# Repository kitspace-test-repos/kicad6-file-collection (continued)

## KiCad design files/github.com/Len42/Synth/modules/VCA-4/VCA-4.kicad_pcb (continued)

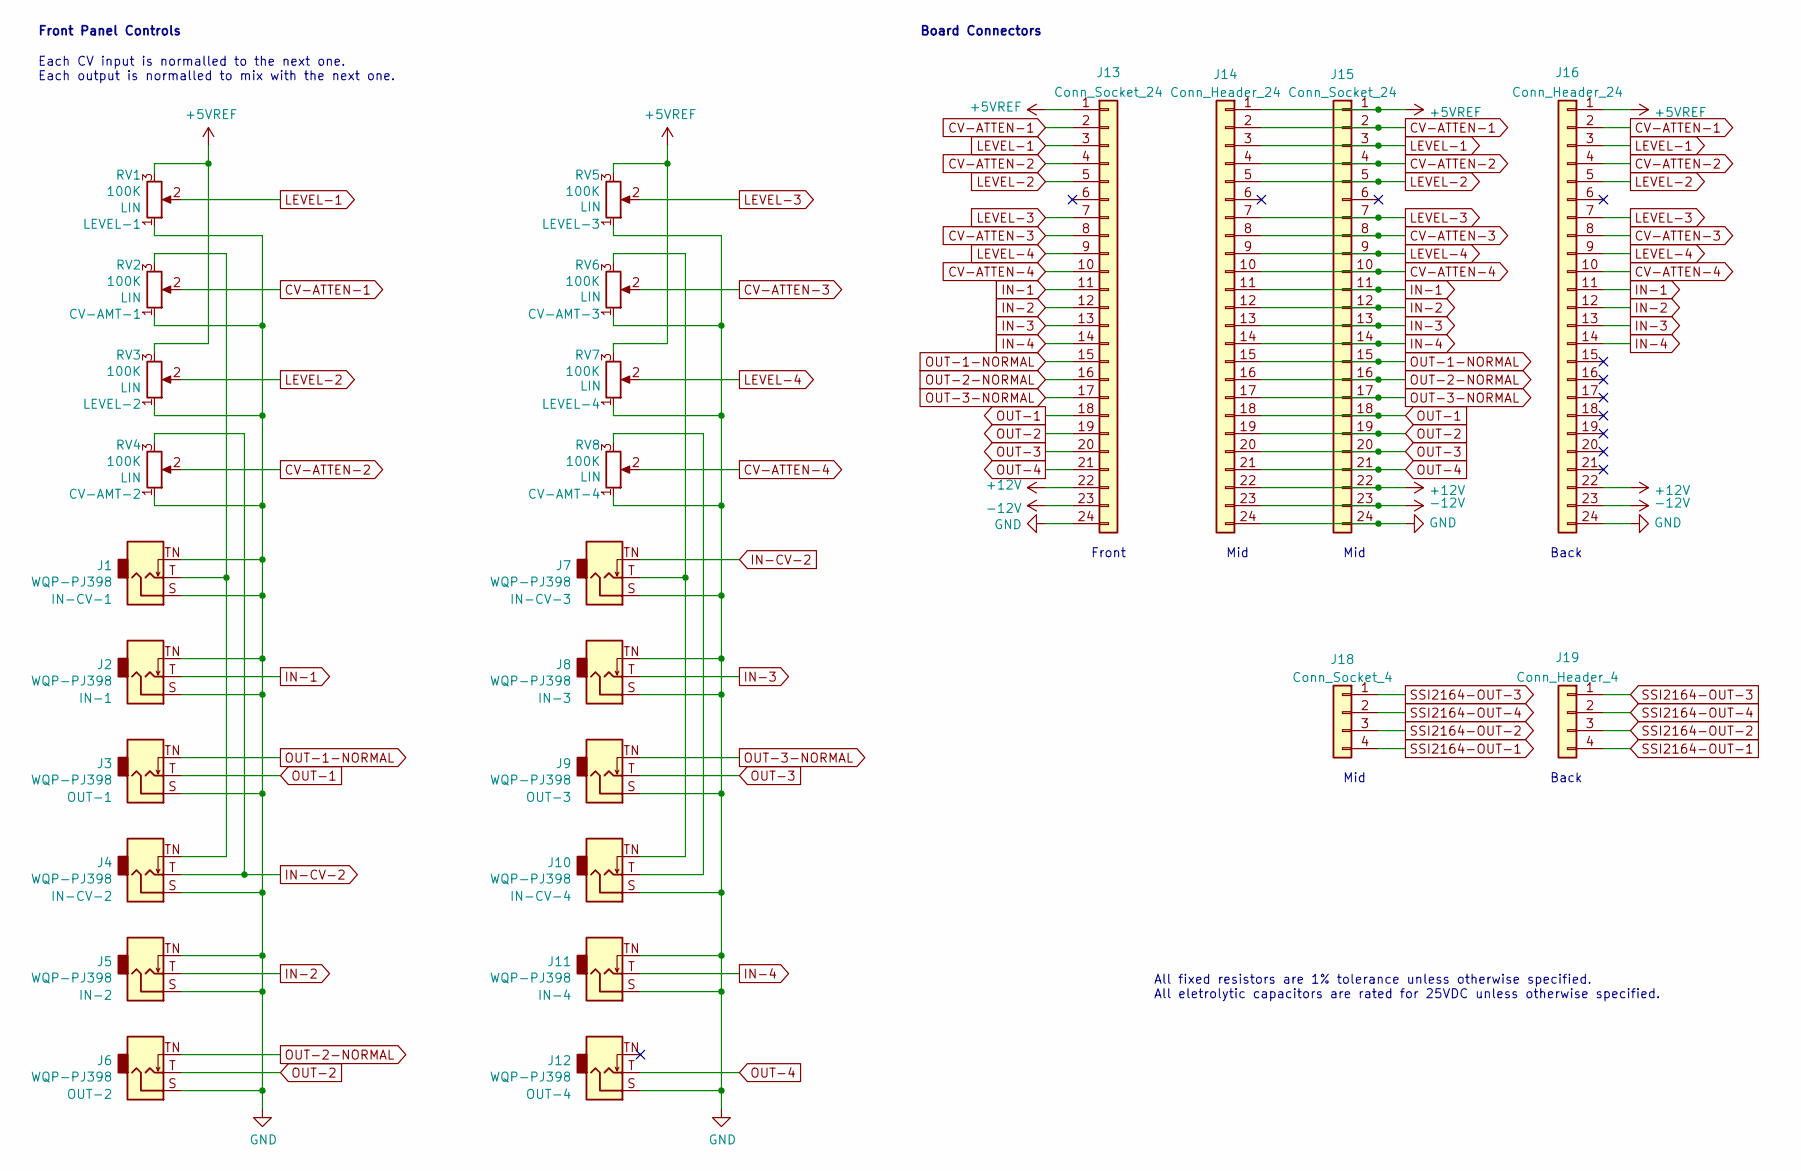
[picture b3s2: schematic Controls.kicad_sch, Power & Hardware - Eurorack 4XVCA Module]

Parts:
J1, J2, J3, J4, J5, J6, J7, J8, J9, J10, J11, J12: WQP-PJ398; Jack_3.5mm_QingPu_WQP-PJ398SM_Vertical; ManufacturerPartNum PJ398SM / WQP518MA
J13, J15: Conn_Socket_24; PinSocket_1x24_P2.54mm_Vertical
J14, J16: Conn_Header_24; PinHeader_1x24_P2.54mm_Vertical
J18: Conn_Socket_4; PinSocket_1x04_P2.54mm_Vertical
J19: Conn_Header_4; PinHeader_1x04_P2.54mm_Vertical
RV1, RV3, RV5, RV7: 100K; Potentiometer_Alpha_RD901F-40-00D_Single_Vertical; ManufacturerPartNum RD901F-40-15R1-B100K-00DL1
RV2, RV4, RV6, RV8: 100K; Potentiometer_SongHuei_Single_Vertical; ManufacturerPartNum R0904N*

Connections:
+5VREF: J13.1, J14.1, J15.1, J16.1, RV1.3, RV3.3, RV5.3, RV7.3; also elsewhere on the board
+12V: J13.22, J14.22, J15.22, J16.22; also elsewhere on the board
-12V: J13.23, J14.23, J15.23, J16.23; also elsewhere on the board
CV-ATTEN-1: J13.2, J14.2, J15.2, J16.2, RV2.2; also elsewhere on the board
CV-ATTEN-2: J13.4, J14.4, J15.4, J16.4, RV4.2; also elsewhere on the board
CV-ATTEN-3: J13.8, J14.8, J15.8, J16.8, RV6.2; also elsewhere on the board
CV-ATTEN-4: J13.10, J14.10, J15.10, J16.10, RV8.2; also elsewhere on the board
GND: J1.S, J1.TN, J2.S, J2.TN, J3.S, J4.S, J5.S, J5.TN, J6.S, J7.S, J8.S, J8.TN, J9.S, J10.S, J11.S, J11.TN, J12.S, J13.24, J14.24, J15.24, J16.24, RV1.1, RV2.1, RV3.1, RV4.1, RV5.1, RV6.1, RV7.1, RV8.1; also elsewhere on the board
IN-1: J2.T, J13.11, J14.11, J15.11, J16.11; also elsewhere on the board
IN-2: J5.T, J13.12, J14.12, J15.12, J16.12; also elsewhere on the board
IN-3: J8.T, J13.13, J14.13, J15.13, J16.13; also elsewhere on the board
IN-4: J11.T, J13.14, J14.14, J15.14, J16.14; also elsewhere on the board
IN-CV-2: J4.T, J7.TN, RV4.3
LEVEL-1: J13.3, J14.3, J15.3, J16.3, RV1.2; also elsewhere on the board
LEVEL-2: J13.5, J14.5, J15.5, J16.5, RV3.2; also elsewhere on the board
LEVEL-3: J13.7, J14.7, J15.7, J16.7, RV5.2; also elsewhere on the board
LEVEL-4: J13.9, J14.9, J15.9, J16.9, RV7.2; also elsewhere on the board
unnamed: J1.T, J4.TN, RV2.3
unnamed: J10.T, RV8.3
unnamed: J7.T, J10.TN, RV6.3
OUT-1: J3.T, J13.18, J14.18, J15.18; also elsewhere on the board
OUT-1-NORMAL: J3.TN, J13.15, J14.15, J15.15; also elsewhere on the board
OUT-2: J6.T, J13.19, J14.19, J15.19; also elsewhere on the board
OUT-2-NORMAL: J6.TN, J13.16, J14.16, J15.16; also elsewhere on the board
OUT-3: J9.T, J13.20, J14.20, J15.20; also elsewhere on the board
OUT-3-NORMAL: J9.TN, J13.17, J14.17, J15.17; also elsewhere on the board
OUT-4: J12.T, J13.21, J14.21, J15.21; also elsewhere on the board
SSI2164-OUT-1: J18.4, J19.4; also elsewhere on the board
SSI2164-OUT-2: J18.3, J19.3; also elsewhere on the board
SSI2164-OUT-3: J18.1, J19.1; also elsewhere on the board
SSI2164-OUT-4: J18.2, J19.2; also elsewhere on the board

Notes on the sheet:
All fixed resistors are 1% tolerance unless otherwise specified. All eletrolytic capacitors are rated for 25VDC unless otherwise specified.
Back
Mid
Board Connectors
Each CV input is normalled to the next one. Each output is normalled to mix with the next one.
Front
Front Panel Controls

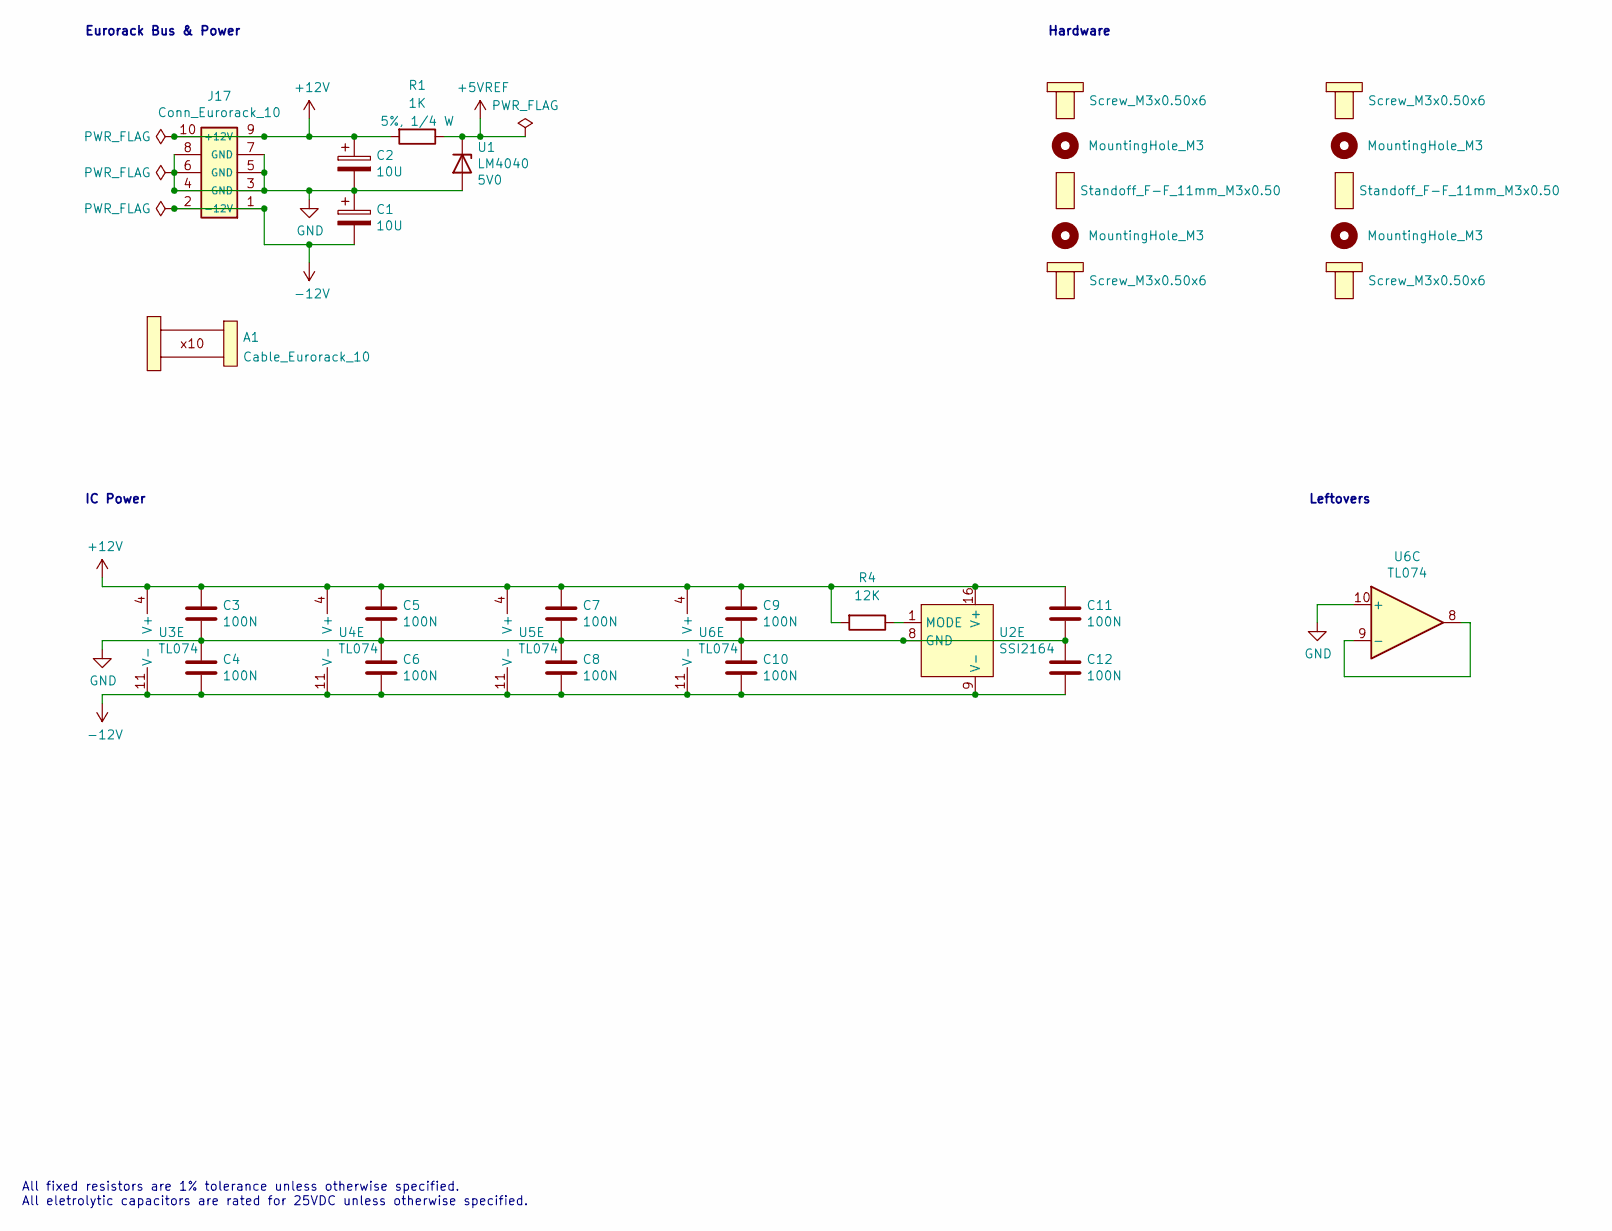
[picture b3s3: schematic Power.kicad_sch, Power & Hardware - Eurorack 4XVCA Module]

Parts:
A1: Cable_Eurorack_10; NoFootprint
C1, C2: 10U; CP_Radial_D4.0mm_P1.50mm; ManufacturerPartNum EEA-FC1E100
C3, C4, C5, C6, C7, C8, C9, C10, C11, C12: 100N; C_Disc_D5.0mm_W2.5mm_P2.50mm; ManufacturerPartNum FG18X7R1H104KNT06
H1, H5, H6, H10: Screw_M3x0.50x6
H2, H4, H7, H9: MountingHole_M3; MountingHole_PCB_3.2mm_M3
H3, H8: Standoff_F-F_11mm_M3x0.50; ManufacturerPartNum 05.03.111
J17: Conn_Eurorack_10; IDC-Header-Eurorack-10-TH; ManufacturerPartNum 61201021621
R1: 1K; R_Axial_DIN0207_L6.3mm_D2.5mm_P10.16mm_Horizontal; ManufacturerPartNum CCF071K00JKE36
R4: 12K; R_Axial_DIN0207_L6.3mm_D2.5mm_P7.62mm_Horizontal; ManufacturerPartNum MFR-12FTF52-12K
U1: LM4040; TO-92-2_Wide; ManufacturerPartNum LM4040BIZ-5.0/NOPB
U2: SSI2164; Breakout_DIP-SOIC-16_W15.24mm; ManufacturerPartNum SSI2164
U3, U4, U5, U6: TL074; DIP-14_W7.62mm; ManufacturerPartNum TL074BCN

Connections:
+5VREF: R1.1, U1.1 (K); also elsewhere on the board
+12V: C2.1, C3.1, C5.1, C7.1, C9.1, C11.1, J17.9 (+12V), J17.10, R1.2, R4.2, U2.16 (V+), U3.4 (V+), U4.4 (V+), U5.4 (V+), U6.4 (V+); also elsewhere on the board
-12V: C1.2, C4.2, C6.2, C8.2, C10.2, C12.2, J17.1 (-12V), J17.2, U2.9 (V-), U3.11 (V-), U4.11 (V-), U5.11 (V-), U6.11 (V-); also elsewhere on the board
GND: C1.1, C2.2, C3.2, C4.1, C5.2, C6.1, C7.2, C8.1, C9.2, C10.1, C11.2, C12.1, J17.3 (GND), J17.4, J17.5 (GND), J17.6, J17.7 (GND), J17.8, U1.2 (A), U2.8 (GND), U6.10 (+); also elsewhere on the board
unnamed: R4.1, U2.1 (MODE)
unnamed: U6.8, U6.9 (-)

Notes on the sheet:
IC Power
Leftovers
Eurorack Bus & Power
All fixed resistors are 1% tolerance unless otherwise specified. All eletrolytic capacitors are rated for 25VDC unless otherwise specified.
Hardware

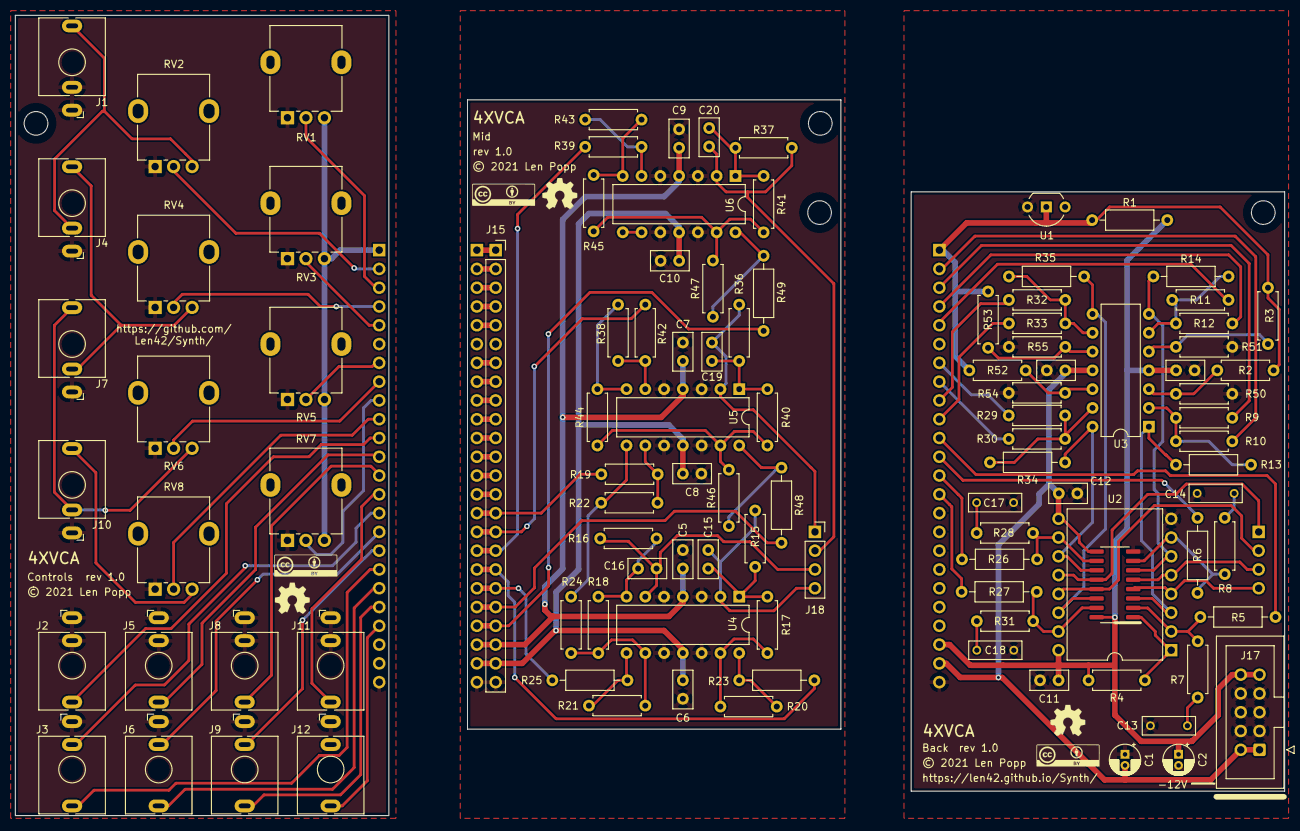
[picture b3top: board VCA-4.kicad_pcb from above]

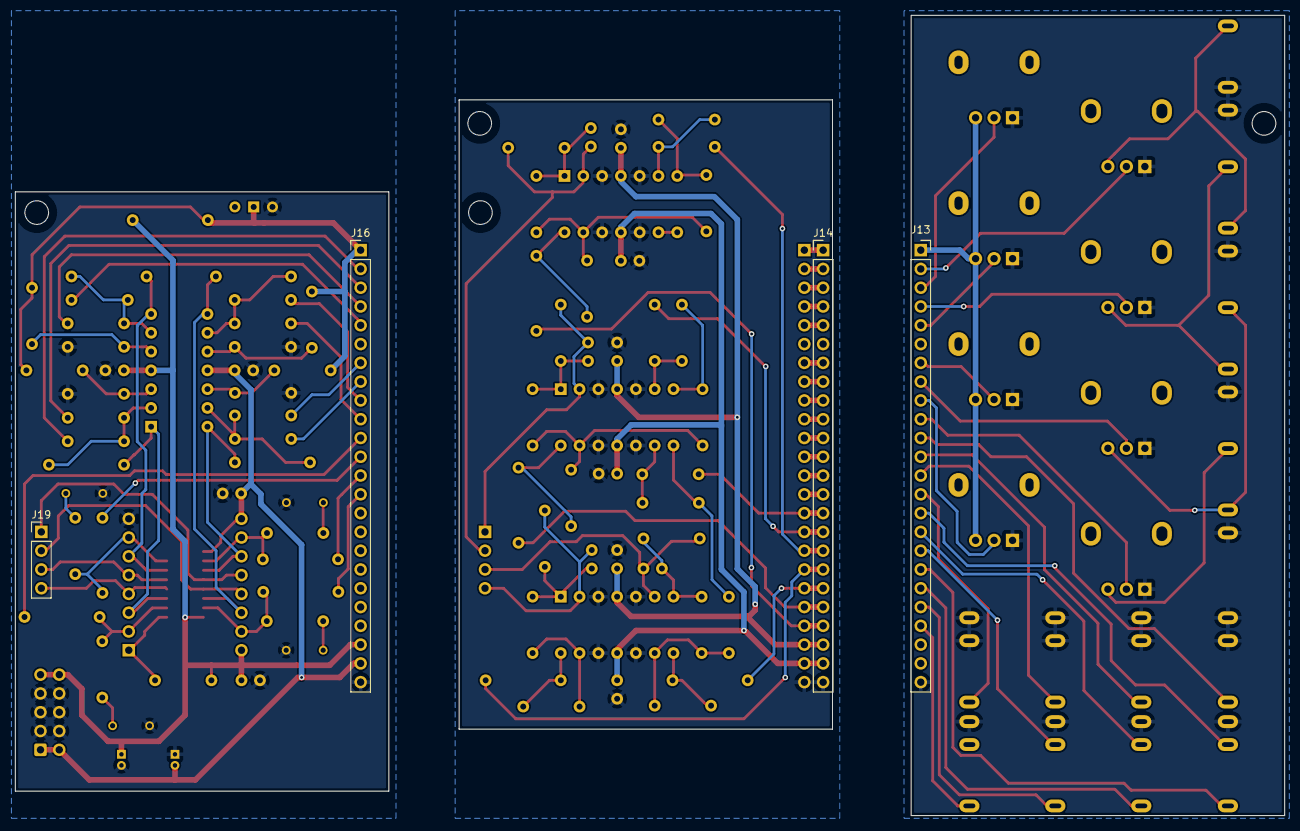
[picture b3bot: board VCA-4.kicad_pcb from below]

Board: 2 copper layers, 171.6 x 108.2 mm, 118 parts (4 on the bottom side), 71 nets.

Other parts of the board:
G2, G2#2, G2#3: Logo_CC_BY
G4, G4#2, G4#3: Logo_OSHW

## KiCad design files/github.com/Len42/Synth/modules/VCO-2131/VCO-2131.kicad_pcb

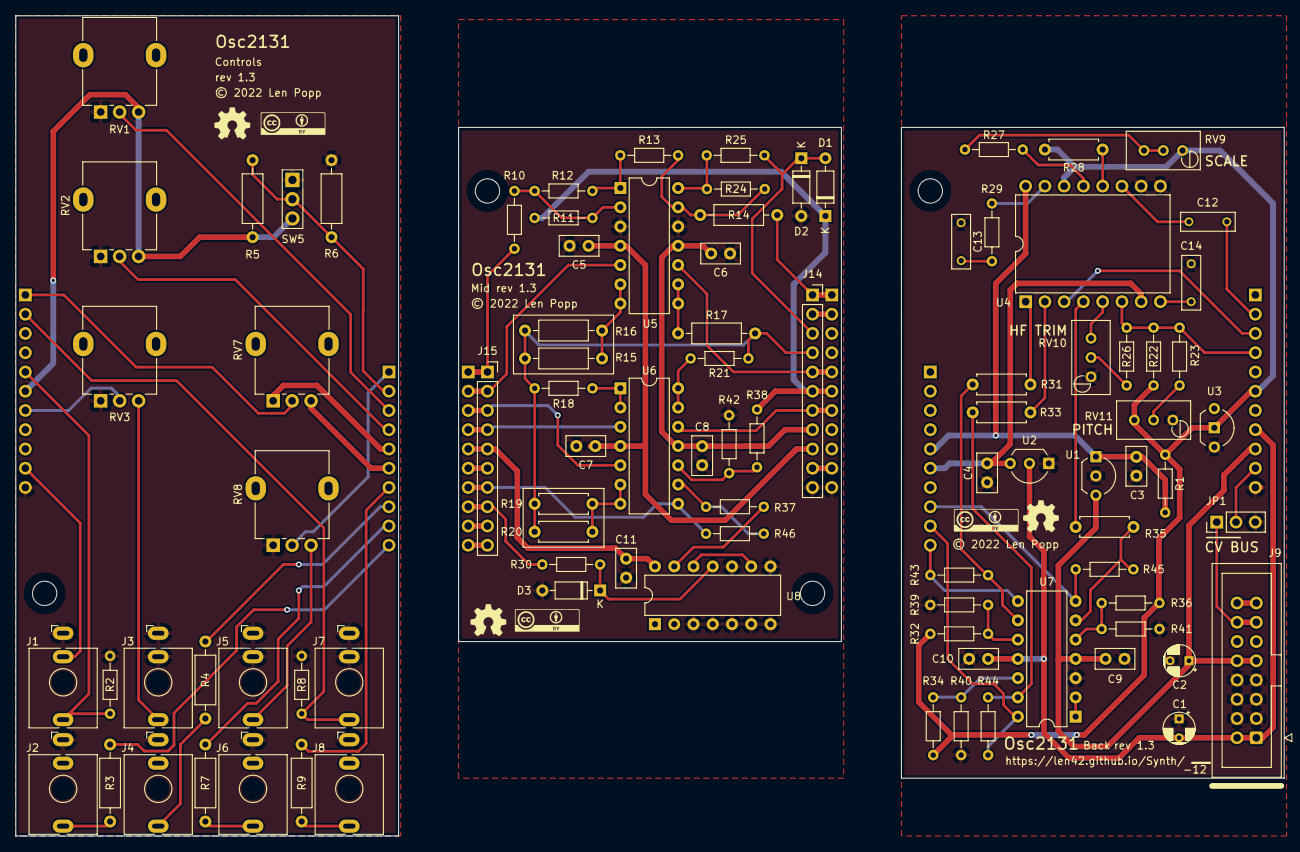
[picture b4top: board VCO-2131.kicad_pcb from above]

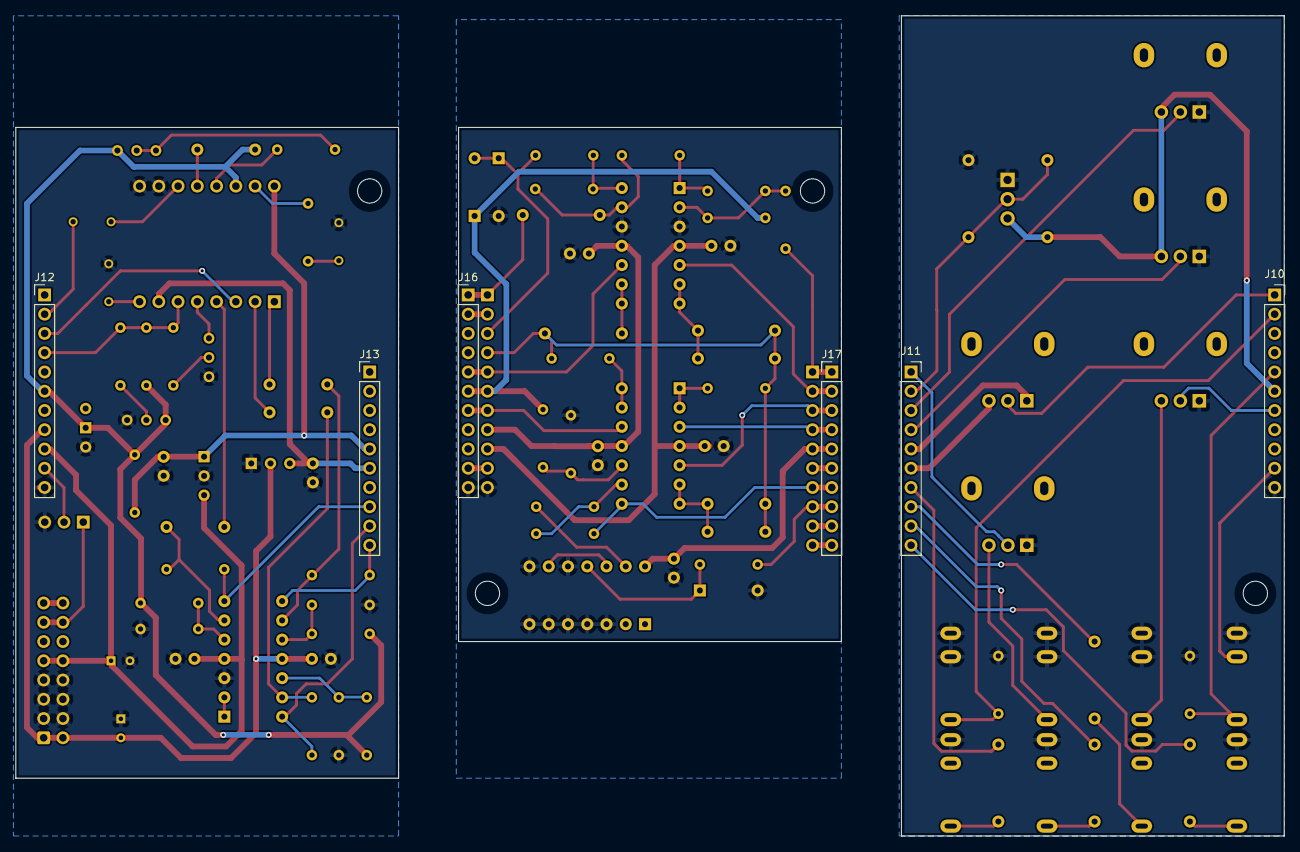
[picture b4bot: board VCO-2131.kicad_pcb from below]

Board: 2 copper layers, 167.3 x 108.2 mm, 104 parts (6 on the bottom side), 63 nets.

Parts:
C1, C2: 10U; CP_Radial_D4.0mm_P2.50mm
C3, C4, C5, C6, C7, C8, C9, C10, C11: 100N; C_Disc_D5.0mm_W2.5mm_P2.50mm
C12, C13: 10N; C_Rect_Kemet_L7.2mm_W2.5mm_P5mm
C14: 3N9; C_Rect_Kemet_L7.2mm_W2.5mm_P5mm
D1, D2, D3: 1N5711; D_DO-35_SOD27_P7.62mm_Horizontal
G1, G6: Logo_CC_BY
G2, G3, G4: Logo_OSHW
G5: Logo_CC_BY_SA; Logo_CC_BY
J1, J2, J3, J4, J5, J6, J7, J8: WQP-PJ398; Jack_3.5mm_QingPu_WQP-PJ398SM_Vertical
J9: Conn_Eurorack_16; IDC-Header-Eurorack-16-TH
J10: Conn_Front_Left; PinSocket_1x11_P2.54mm_Vertical
J11: Conn_Front_Right; PinSocket_1x10_P2.54mm_Vertical
J12: Conn_Back_Right; PinHeader_1x11_P2.54mm_Vertical
J13: Conn_Back_Left; PinHeader_1x10_P2.54mm_Vertical
J14: Conn_Passthru_Right; PinSocket_1x11_P2.54mm_Vertical
J15: Conn_Passthru_Left; PinSocket_1x10_P2.54mm_Vertical
J16: Conn_Mid_Right; PinHeader_1x11_P2.54mm_Vertical
J17: Conn_Mid_Left; PinHeader_1x10_P2.54mm_Vertical
JP1: CV-BUS; PinHeader_1x03_P2.54mm_Vertical
R1: 470R; R_Axial_DIN0204_L3.6mm_D1.6mm_P7.62mm_Horizontal
R2: 4M7; R_Axial_DIN0204_L3.6mm_D1.6mm_P7.62mm_Horizontal
R3, R4, R7, R9: 1K; R_Axial_DIN0207_L6.3mm_D2.5mm_P10.16mm_Horizontal
R5, R6, R17: 100K; R_Axial_DIN0207_L6.3mm_D2.5mm_P10.16mm_Horizontal
R8, R21, R22, R23, R25: 100K; R_Axial_DIN0204_L3.6mm_D1.6mm_P7.62mm_Horizontal
R10, R13: 150K; R_Axial_DIN0204_L3.6mm_D1.6mm_P7.62mm_Horizontal
R11, R12, R24: 75K; R_Axial_DIN0204_L3.6mm_D1.6mm_P7.62mm_Horizontal
R14: 300K; R_Axial_DIN0207_L6.3mm_D2.5mm_P10.16mm_Horizontal
R15, R16: 125K; R_Axial_DIN0207_L6.3mm_D2.5mm_P10.16mm_Horizontal
R18: 62K; R_Axial_DIN0204_L3.6mm_D1.6mm_P7.62mm_Horizontal
R19, R20: 1M5; R_Axial_DIN0207_L6.3mm_D2.5mm_P7.62mm_Horizontal
R26: 270K; R_Axial_DIN0204_L3.6mm_D1.6mm_P7.62mm_Horizontal
R27: 47K; R_Axial_DIN0204_L3.6mm_D1.6mm_P7.62mm_Horizontal
R28: 499K; R_Axial_DIN0207_L6.3mm_D2.5mm_P7.62mm_Horizontal
R29: 270R; R_Axial_DIN0204_L3.6mm_D1.6mm_P7.62mm_Horizontal
R30: 10K; R_Axial_DIN0204_L3.6mm_D1.6mm_P7.62mm_Horizontal
R31, R33, R35: 9K; R_Axial_DIN0207_L6.3mm_D2.5mm_P7.62mm_Horizontal
R32, R34, R36, R42, R43, R44, R45, R46: 36K; R_Axial_DIN0204_L3.6mm_D1.6mm_P7.62mm_Horizontal
R37, R38: 18K; R_Axial_DIN0204_L3.6mm_D1.6mm_P7.62mm_Horizontal
R39, R40, R41: 24K; R_Axial_DIN0204_L3.6mm_D1.6mm_P7.62mm_Horizontal
RV1, RV2, RV3, RV7, RV8: 100K; Potentiometer_Alpha_RD901F-40-00D_Single_Vertical
RV9, RV10, RV11: 5K; Potentiometer_Bourns_3296W_Vertical
SW5: ON_OFF_ON; SW_SPDT_THT_2.54
U1: L78L05; TO-92_Inline_Wide
U2: L79L05; TO-92_Inline_Wide
U3: LM4040; TO-92-2_Wide
U4: SSI2131; Breakout_DIP-16_W15.24mm
U5, U6, U7: TL074; DIP-14_W7.62mm
U8: CD4013; DIP-14_W7.62mm

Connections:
+5V: C3.1, C11.1, J11.5, J13.5, J15.5, J17.5, R1.2, RV7.1, U1.1 (VO), U4.16 (V+), U8.14 (VDD)
+12V: C2.1, C5.1, C7.1, C9.1, J9.9 (+12V), J9.10, J12.9, J14.9, U1.3 (VI), U5.4 (V+), U6.4 (V+), U7.4 (V+)
-5V: C4.2, J11.6, J13.6, J15.6, J17.6, RV7.3, U2.3 (VO), U4.7 (V-)
-12V: C1.2, C6.2, C8.2, C10.2, J9.1 (-12V), J9.2, J12.8, J14.8, U2.2 (VI), U5.11 (V-), U6.11 (V-), U7.11 (V-)
CV-FREQ-1VOCT: J1.T, J10.5, J14.5, J16.5, R2.1, U5.10 (+)
CV-FREQ-BUS: J1.TN, J10.10, J12.10, J14.10, J16.10, JP1.2 (C)
CV-FREQ-COARSE: J11.4, J15.4, J17.4, RV2.2, U6.3 (+)
CV-FREQ-FINE: J11.3, J15.3, J17.3, RV1.2, U6.5 (+)
CV-FREQ-MOD: J10.7, J14.7, J16.7, RV3.2, U6.12 (+)
CV-FREQ-MOD-IN: J3.T, RV3.3
CV-FREQ-OCTAVE: J11.2, J15.2, J17.2, R5.2, R6.2, SW5.2, U5.5 (+)
CV-PW-MOD: J11.1, J15.1, J17.1, R10.2, RV8.2
CV-PW-MOD-IN: J5.T, RV8.3
CV-PW-POT: J10.1, J14.1, J16.1, R14.2, RV7.2
EXPO-FREQ-2131: J12.4, J14.4, R15.1, R16.1, R17.1, R18.1, R19.1, R20.1, R21.1, R22.1, R23.1, R26.2, U4.6 (EXPO-FREQ)
GND: C1.1, C2.2, C3.2, C4.1, C5.2, C6.1, C7.2, C8.1, C9.2, C10.1, C11.2, C13.1, C14.2, D2.2 (A), D3.2 (A), J1.S, J2.S, J3.S, J3.TN, J4.S, J5.S, J5.TN, J6.S, J7.S, J7.TN, J8.S, J9.3 (GND), J9.4, J9.5 (GND), J9.6, J9.7 (GND), J9.8, J10.11, J12.11, J14.11, J16.11, JP1.3 (B), R2.2, R6.1, R8.2, R39.2, R40.2, R41.2, R42.2, RV1.1, RV2.1, RV3.1, RV8.1, RV10.1, RV11.1, SW5.1, U1.2 (GND), U2.1 (GND), U3.2 (A), U4.9 (GND), U4.10 (SYNC-H), U5.3 (+), U5.12 (+), U7.3 (+), U8.3 (C), U8.4 (R), U8.5 (D), U8.6 (S), U8.7 (VSS), U8.8 (S), U8.10 (R)
IN-SYNC: C12.1, J7.T, J10.2, J12.2, J14.2, J16.2, R8.1
unnamed: C12.2, U4.11 (SYNC-S)
unnamed: C13.2, R29.2
unnamed: C14.1, U4.8 (TCAP)
unnamed: D3.1 (K), R30.1, U8.11 (C)
unnamed: J2.T, R3.2
unnamed: J4.T, R4.2
unnamed: J6.T, R7.2
unnamed: J8.T, R9.2
unnamed: J9.13 (CV), J9.14, JP1.1 (A)
unnamed: J9.15 (GATE), J9.16
unnamed: R10.1, R11.1, R12.2, U5.2 (-)
unnamed: R12.1, R13.2, U5.1
unnamed: R13.1, R14.1, R24.2, U5.13 (-)
unnamed: R15.2, R16.2, U5.6 (-), U5.7
unnamed: R17.2, U5.8, U5.9 (-)
unnamed: R18.2, U6.1, U6.2 (-)
unnamed: R19.2, R20.2, U6.6 (-), U6.7
unnamed: R21.2, U6.13 (-), U6.14
unnamed: R23.2, RV11.2
unnamed: R24.1, R25.2, U5.14
unnamed: R26.1, RV10.2
unnamed: R27.1, RV9.2, RV9.3
unnamed: R27.2, U4.13 (EXPO-SCALE)
unnamed: R28.1, U4.12 (LIN-FREQ)
unnamed: R29.1, U4.15 (BW-COMP)
unnamed: R31.1, R43.2, U7.9 (-)
unnamed: R31.2, U4.1 (SAW)
unnamed: R32.1, R39.1, U7.10 (+)
unnamed: R33.1, R44.2, U7.13 (-)
unnamed: R33.2, U4.2 (PULSE)
unnamed: R34.1, R40.1, U7.12 (+)
unnamed: R35.1, R45.2, U7.6 (-)
unnamed: R35.2, U4.4 (TRI)
unnamed: R36.1, R41.1, U7.5 (+)
unnamed: R37.1, R46.2, U6.9 (-)
unnamed: R37.2, U8.13 (Q)
unnamed: R38.1, R42.1, U6.10 (+)
unnamed: RV10.3, U4.5 (HF-TRACK)
unnamed: U7.1, U7.2 (-)
unnamed: U8.9 (D), U8.12 (~Q)
OUT-PULSE: J11.9, J13.9, J15.9, J17.9, R7.1, R44.1, U7.14
OUT-SAW: J11.10, J13.10, J15.10, J17.10, R3.1, R43.1, U7.8
OUT-SUB: J11.7, J15.7, J17.7, R9.1, R46.1, U6.8
OUT-TRI: J11.8, J13.8, J15.8, J17.8, R4.1, R30.2, R45.1, U7.7
PWM-2131: D1.2 (A), D2.1 (K), J12.3, J14.3, R25.1, U4.3 (PWM)
VREF+: D1.1 (K), J10.6, J12.6, J14.6, J16.6, R1.1, R5.1, R11.2, R22.2, R28.2, R32.2, R34.2, R36.2, R38.2, RV1.3, RV2.3, RV9.1, RV11.3, SW5.3, U3.1 (K), U4.14 (VREF)

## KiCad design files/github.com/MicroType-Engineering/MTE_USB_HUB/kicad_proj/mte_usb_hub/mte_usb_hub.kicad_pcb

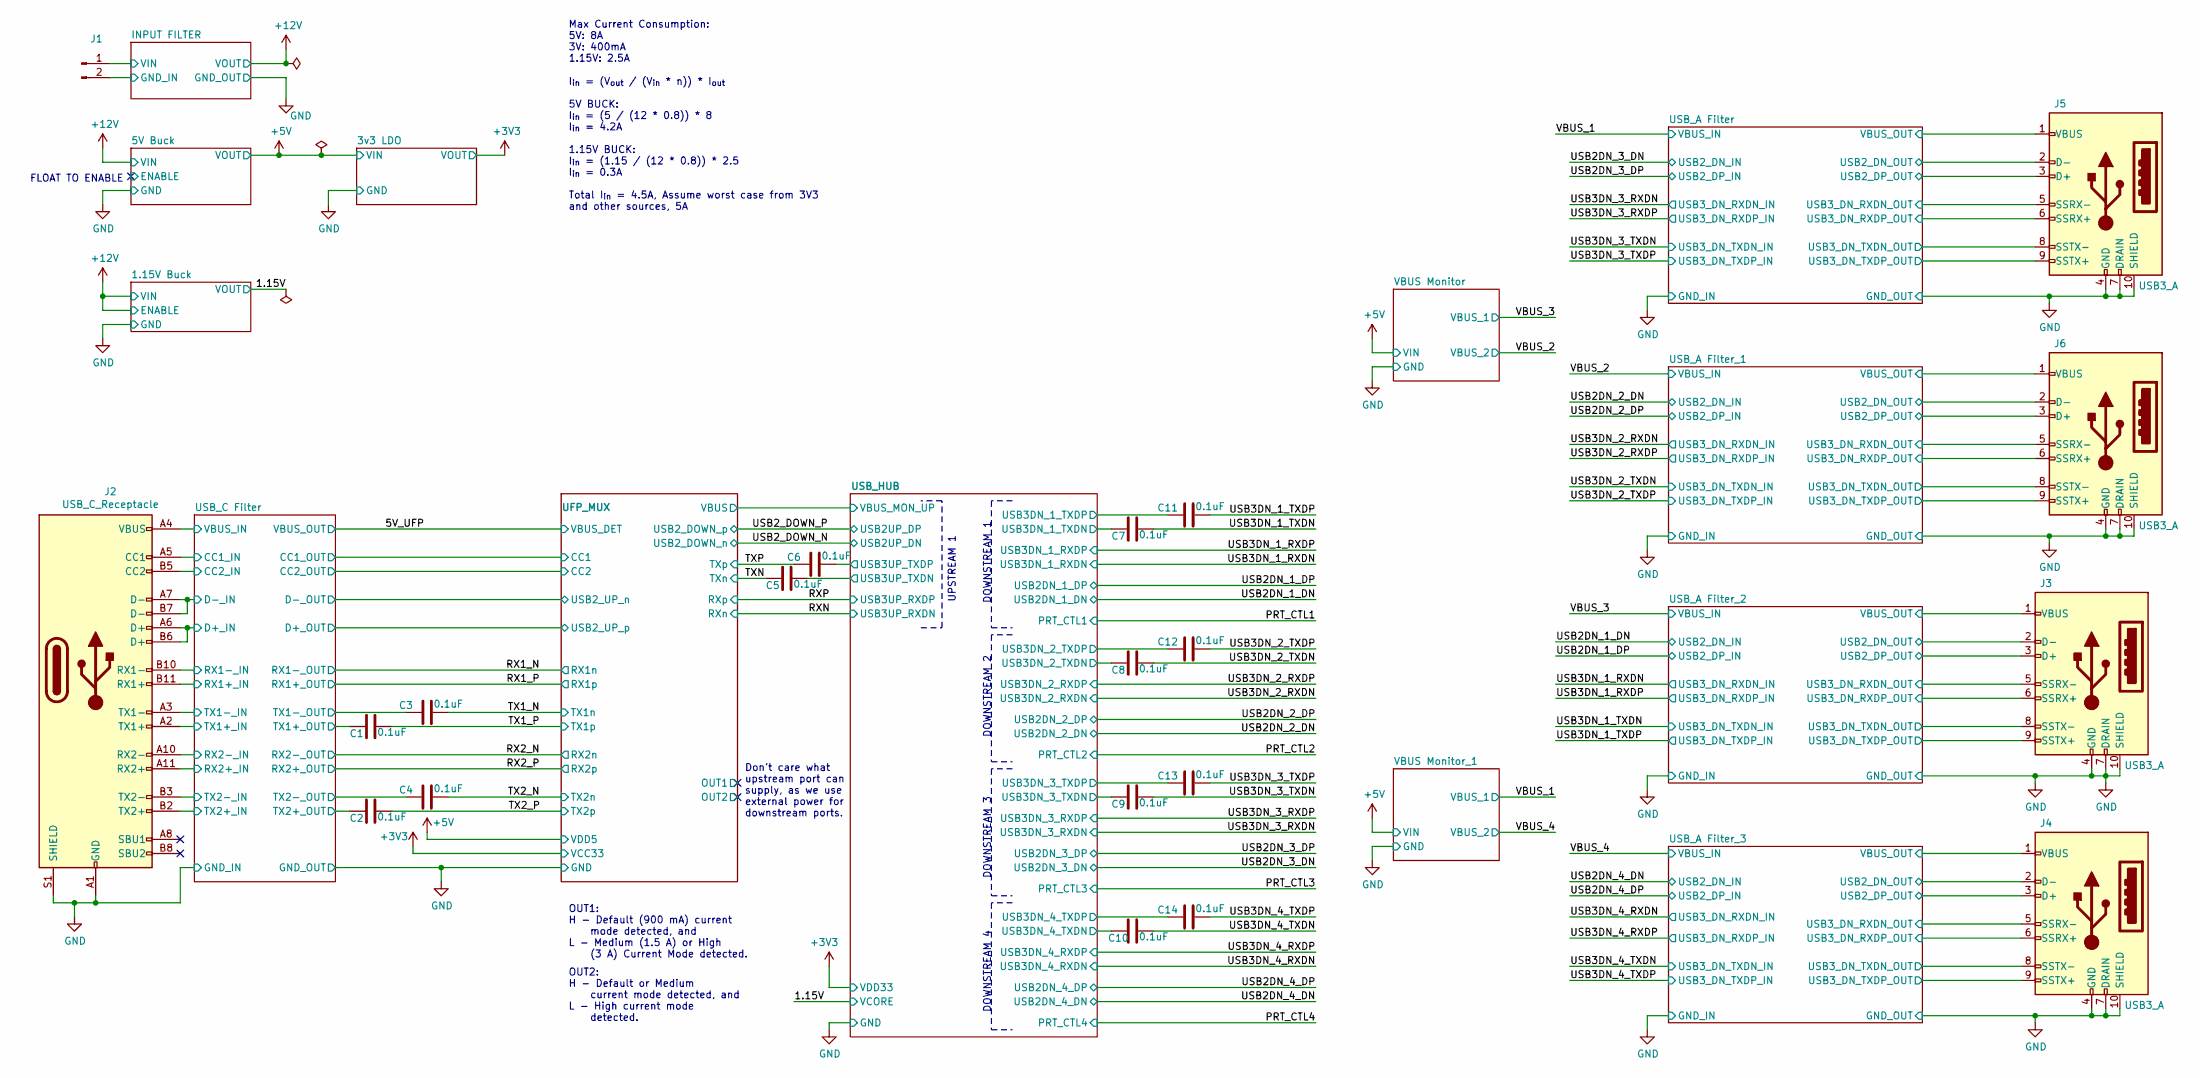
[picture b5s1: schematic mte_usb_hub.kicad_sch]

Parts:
C1, C2, C3, C4, C5, C6, C7, C8, C9, C10, C11, C12, C13, C14: CC0402KRX5R7BB104; CAPACITOR_0402N
J1: Conn_01x02_Male; PinHeader_1x02_P2.54mm_Vertical
J2: USB_C_Receptacle; USB_C_Receptacle_Amphenol_12401610E4-2A
J3, J4, J5, J6: USB3_A; USB3_A_Molex_48393-001

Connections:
/5V_UFP: J2.A4 (VBUS), J2.A9 (VBUS), J2.B4 (VBUS), J2.B9 (VBUS); also elsewhere on the board
/INPUT FILTER/GND_IN: J1.2; also elsewhere on the board
/INPUT FILTER/VIN: J1.1; also elsewhere on the board
/RX1_N: J2.B10 (RX1-); also elsewhere on the board
/RX1_P: J2.B11 (RX1+); also elsewhere on the board
/RX2_N: J2.A10 (RX2-); also elsewhere on the board
/RX2_P: J2.A11 (RX2+); also elsewhere on the board
/TX1_N: C3.2; also elsewhere on the board
/TX1_P: C1.2; also elsewhere on the board
/TX2_N: C4.2; also elsewhere on the board
/TX2_P: C2.2; also elsewhere on the board
/TXN: C5.1; also elsewhere on the board
/TXP: C6.1; also elsewhere on the board
/UFP_MUX/CC1: J2.A5 (CC1); also elsewhere on the board
/UFP_MUX/CC2: J2.B5 (CC2); also elsewhere on the board
/USB2DN_1_DN: J3.2 (D-); also elsewhere on the board
/USB2DN_1_DP: J3.3 (D+); also elsewhere on the board
/USB2DN_2_DN: J6.2 (D-); also elsewhere on the board
/USB2DN_2_DP: J6.3 (D+); also elsewhere on the board
/USB2DN_3_DN: J5.2 (D-); also elsewhere on the board
/USB2DN_3_DP: J5.3 (D+); also elsewhere on the board
/USB2DN_4_DN: J4.2 (D-); also elsewhere on the board
/USB2DN_4_DP: J4.3 (D+); also elsewhere on the board
/USB2_DOWN_N: J2.A7 (D-), J2.B7 (D-); also elsewhere on the board
/USB2_DOWN_P: J2.A6 (D+), J2.B6 (D+); also elsewhere on the board
/USB3DN_1_RXDN: J3.5 (SSRX-); also elsewhere on the board
/USB3DN_1_RXDP: J3.6 (SSRX+); also elsewhere on the board
/USB3DN_1_TXDN: C7.2, J3.8 (SSTX-); also elsewhere on the board
/USB3DN_1_TXDP: C11.2, J3.9 (SSTX+); also elsewhere on the board
/USB3DN_2_RXDN: J6.5 (SSRX-); also elsewhere on the board
/USB3DN_2_RXDP: J6.6 (SSRX+); also elsewhere on the board
/USB3DN_2_TXDN: C8.2, J6.8 (SSTX-); also elsewhere on the board
/USB3DN_2_TXDP: C12.2, J6.9 (SSTX+); also elsewhere on the board
/USB3DN_3_RXDN: J5.5 (SSRX-); also elsewhere on the board
/USB3DN_3_RXDP: J5.6 (SSRX+); also elsewhere on the board
/USB3DN_3_TXDN: C9.2, J5.8 (SSTX-); also elsewhere on the board
/USB3DN_3_TXDP: C13.2, J5.9 (SSTX+); also elsewhere on the board
/USB3DN_4_RXDN: J4.5 (SSRX-); also elsewhere on the board
/USB3DN_4_RXDP: J4.6 (SSRX+); also elsewhere on the board
/USB3DN_4_TXDN: C10.2, J4.8 (SSTX-); also elsewhere on the board
/USB3DN_4_TXDP: C14.2, J4.9 (SSTX+); also elsewhere on the board
/USB_C Filter/_TX1+: C1.1, J2.A2 (TX1+); also elsewhere on the board
/USB_C Filter/_TX1-: C3.1, J2.A3 (TX1-); also elsewhere on the board
/USB_C Filter/_TX2+: C2.1, J2.B2 (TX2+); also elsewhere on the board
/USB_C Filter/_TX2-: C4.1, J2.B3 (TX2-); also elsewhere on the board
/USB_HUB/USB3DN_1_TXDN: C7.1; also elsewhere on the board
/USB_HUB/USB3DN_1_TXDP: C11.1; also elsewhere on the board
/USB_HUB/USB3DN_2_TXDN: C8.1; also elsewhere on the board
/USB_HUB/USB3DN_2_TXDP: C12.1; also elsewhere on the board
/USB_HUB/USB3DN_3_TXDN: C9.1; also elsewhere on the board
/USB_HUB/USB3DN_3_TXDP: C13.1; also elsewhere on the board
/USB_HUB/USB3DN_4_TXDN: C10.1; also elsewhere on the board
/USB_HUB/USB3DN_4_TXDP: C14.1; also elsewhere on the board
/USB_HUB/USB3UP_TXDN: C5.2; also elsewhere on the board
/USB_HUB/USB3UP_TXDP: C6.2; also elsewhere on the board
/VBUS_1: J5.1 (VBUS); also elsewhere on the board
/VBUS_2: J6.1 (VBUS); also elsewhere on the board
/VBUS_3: J3.1 (VBUS); also elsewhere on the board
/VBUS_4: J4.1 (VBUS); also elsewhere on the board
GND: J2.A1 (GND), J2.A12 (GND), J2.B1 (GND), J2.B12 (GND), J2.S1 (SHIELD), J3.4 (GND), J3.7 (DRAIN), J3.10 (SHIELD), J4.4 (GND), J4.7 (DRAIN), J4.10 (SHIELD), J5.4 (GND), J5.7 (DRAIN), J5.10 (SHIELD), J6.4 (GND), J6.7 (DRAIN), J6.10 (SHIELD); also elsewhere on the board

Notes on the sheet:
FLOAT TO ENABLE
Max Current Consumption: 5V: 8A 3V: 400mA 1.15V: 2.5A
I_{in} = (V_{out} / (V_{in} * n)) * I_{out} 5V BUCK: I_{in} = (5 / (12 * 0.8)) * 8 I_{in} = 4.2A 1.15V BUCK: I_{in} = (1.15 / (12 * 0.8)) * 2.5 I_{in} = 0.3A Total I_{in} = 4.5A, Assume worst case from 3V3 and other sources, 5A
OUT1: H - Default (900 mA) current mode detected, and L - Medium (1.5 A) or High (3 A) Current Mode detected.
OUT2: H - Default or Medium current mode detected, and L - High current mode detected.
Don't care what upstream port can supply, as we use external power for downstream ports.
UPSTREAM 1
DOWNSTREAM 1
DOWNSTREAM 2
DOWNSTREAM 3
DOWNSTREAM 4

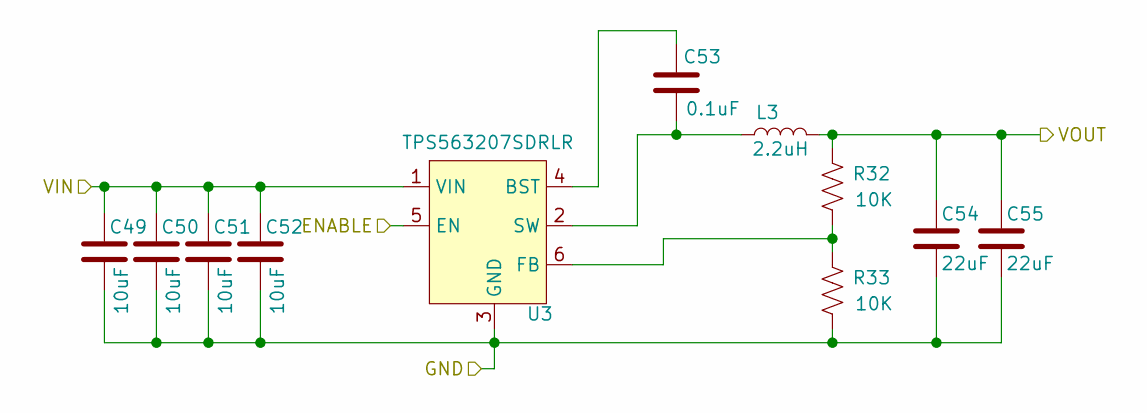
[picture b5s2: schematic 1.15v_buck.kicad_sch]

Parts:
C49, C50, C51, C52: GRM31CR71E106KA12L; CAPACITOR_1206N
C53: CC0402KRX5R7BB104; CAPACITOR_0402N
C54, C55: CL21A226MOCLRNC; CAPACITOR_0805N
L3: 74405042022; INDM400X400X200L95X310N
R32, R33: RC0402JR-0710KL; RESISTOR_0402N
U3: TPS563207SDRLR; SOL6P50_160X160X60L21N

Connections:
+12V: C49.1, C50.1, C51.1, C52.1, U3.1 (VIN), U3.5 (EN); also elsewhere on the board
/1.15V: C54.1, C55.1, L3.2, R32.1; also elsewhere on the board
GND: C49.2, C50.2, C51.2, C52.2, C54.2, C55.2, R33.2, U3.3 (GND); also elsewhere on the board
unnamed: C53.1, L3.1, U3.2 (SW)
unnamed: C53.2, U3.4 (BST)
unnamed: R32.2, R33.1, U3.6 (FB)

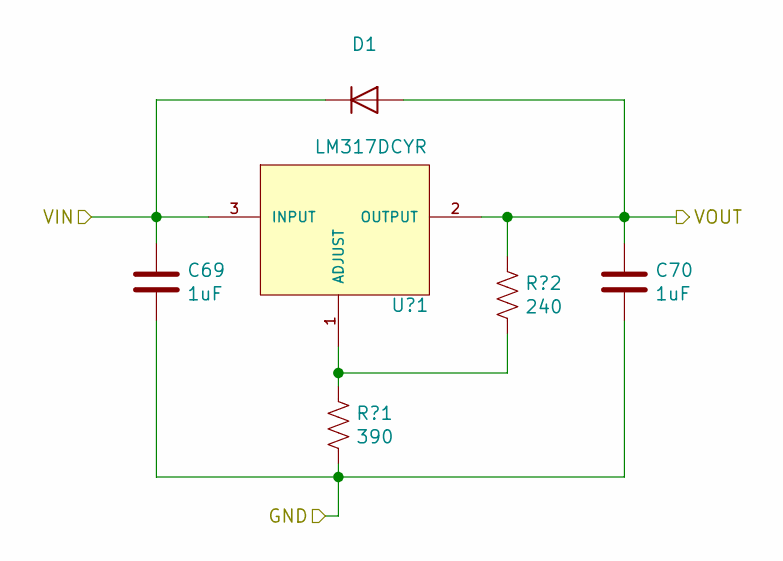
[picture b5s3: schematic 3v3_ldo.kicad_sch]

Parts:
C69, C70: CC0402KRX5R7BB105; CAPACITOR_0402N
D1: BAS16GWJ; SODFL360X160X130L45X62N
R?1: RC0402FR-07390RL; RESISTOR_0402N
R?2: RC0402JR-07240RL; RESISTOR_0402N
U?1: LM317DCYR; SOT223-4P230_700X180L80X75N

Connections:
+3V3: C70.1, D1.A, R?2.1, U?1.2 (OUTPUT), U?1.4 (OUTPUT); also elsewhere on the board
+5V: C69.1, D1.C (K), U?1.3 (INPUT); also elsewhere on the board
GND: C69.2, C70.2, R?1.2; also elsewhere on the board
unnamed: R?1.1, R?2.2, U?1.1 (ADJUST)
